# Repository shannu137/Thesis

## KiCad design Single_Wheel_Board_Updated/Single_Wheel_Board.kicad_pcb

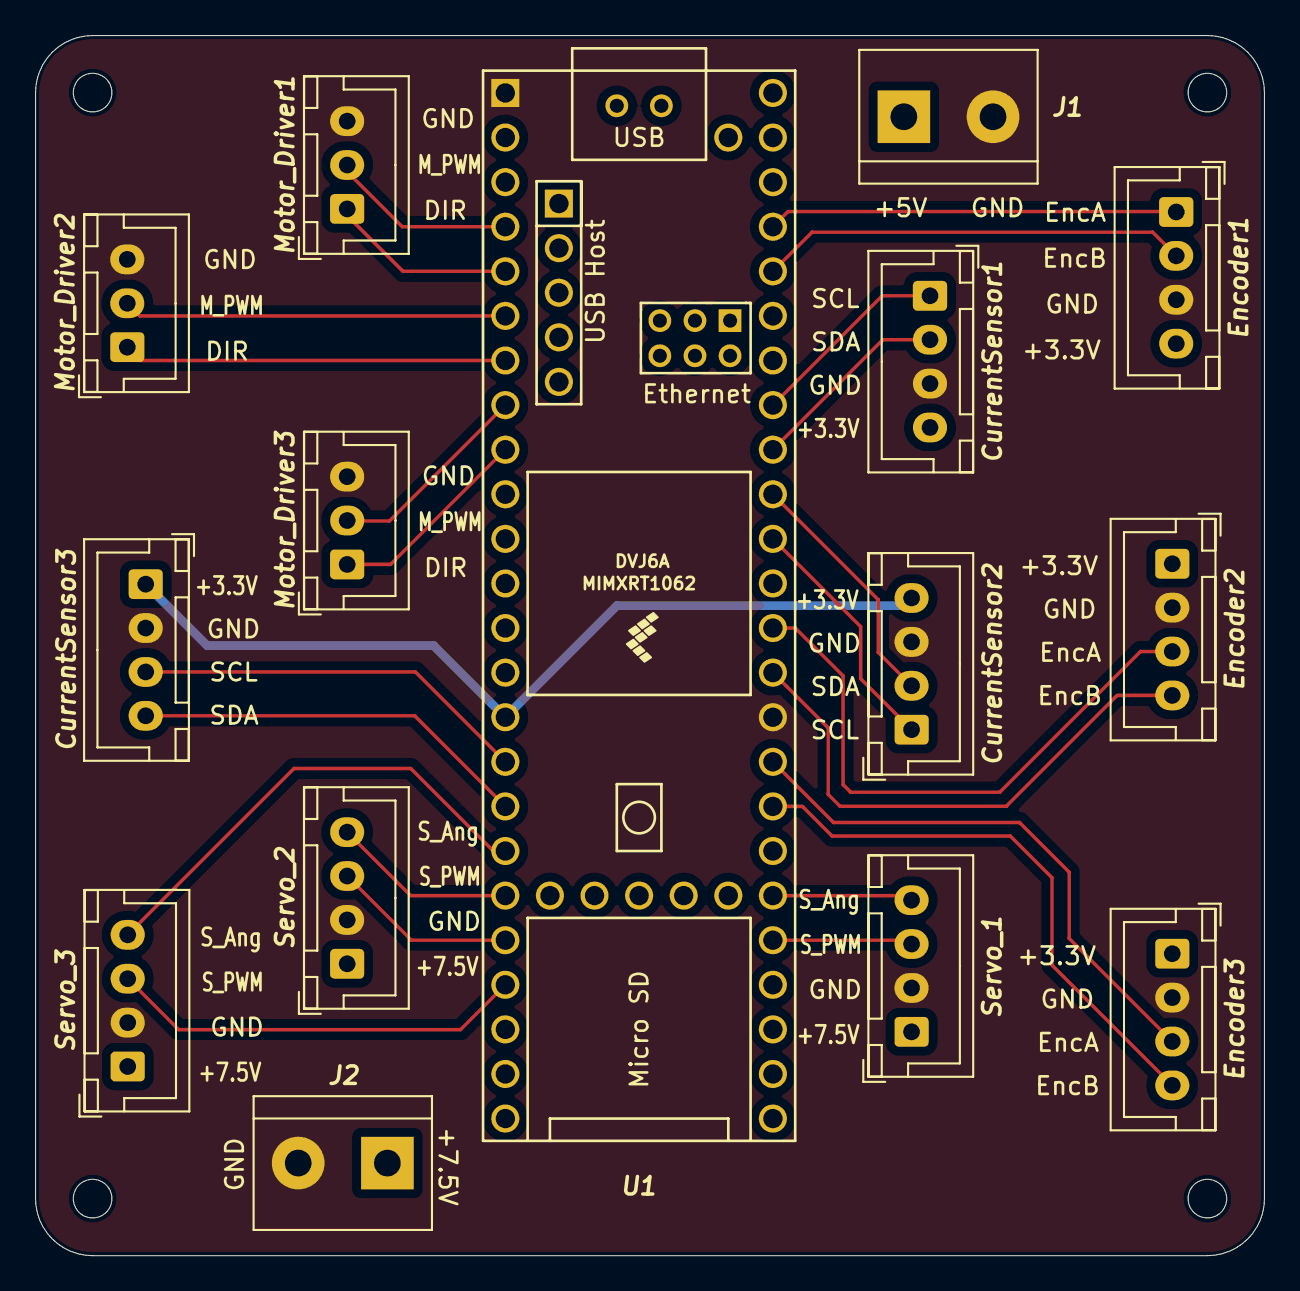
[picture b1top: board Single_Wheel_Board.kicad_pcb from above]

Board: 2 copper layers, 70.0 x 69.5 mm, 15 parts (0 on the bottom side), 28 nets.

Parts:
CurrentSensor1, CurrentSensor2, CurrentSensor3: Conn_01x04; JST_XH_B4B-XH-A_1x04_P2.50mm_Vertical
Encoder1, Encoder2, Encoder3: Conn_01x04; JST_XH_B4B-XH-A_1x04_P2.50mm_Vertical
J1, J2: Screw_Terminal_01x02; TerminalBlock_bornier-2_P5.08mm
Motor_Driver1, Motor_Driver2, Motor_Driver3: Conn_01x03; JST_XH_B3B-XH-A_1x03_P2.50mm_Vertical
Servo_1, Servo_2, Servo_3: Conn_01x04; JST_XH_B4B-XH-A_1x04_P2.50mm_Vertical
U1: Teensy4.1; Teensy41

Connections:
+3.3V: CurrentSensor1.4, CurrentSensor2.4, CurrentSensor3.1, Encoder1.4, Encoder2.1, Encoder3.1, U1.15 (3V3)
+5V: J1.1, U1.48 (VIN)
+7.5V: J2.1, Servo_1.1, Servo_2.1, Servo_3.1
DIR1: Motor_Driver1.1, U1.5 (3_LRCLK2)
DIR2: Motor_Driver2.1, U1.7 (5_IN2)
DIR3: Motor_Driver3.1, U1.9 (7_RX2_OUT1A)
EncA1: Encoder1.1, U1.45 (23_A9_CRX1_MCLK1)
EncA2: Encoder2.3, U1.36 (14_A0_TX3_SPDIF_OUT)
EncA3: Encoder3.3, U1.33 (41_A17)
EncB1: Encoder1.2, U1.44 (22_A8_CTX1)
EncB2: Encoder2.4, U1.35 (13_SCK_LED)
EncB3: Encoder3.4, U1.32 (40_A16)
GND: CurrentSensor1.3, CurrentSensor2.3, CurrentSensor3.2, Encoder1.3, Encoder2.2, Encoder3.2, J1.2, J2.2, Motor_Driver1.3, Motor_Driver2.3, Motor_Driver3.3, Servo_1.2, Servo_2.2, Servo_3.2, U1.1 (GND), U1.34 (GND)
M_PWM1: Motor_Driver1.2, U1.4 (2_OUT2)
M_PWM2: Motor_Driver2.2, U1.6 (4_BCLK2)
M_PWM3: Motor_Driver3.2, U1.8 (6_OUT1D)
SCL1: CurrentSensor1.1, U1.41 (19_A5_SCL)
SCL2: CurrentSensor2.1, U1.38 (16_A2_RX4_SCL1)
SCL3: CurrentSensor3.3, U1.16 (24_A10_TX6_SCL2)
SDA1: CurrentSensor1.2, U1.40 (18_A4_SDA)
SDA2: CurrentSensor2.2, U1.39 (17_A3_TX4_SDA1)
SDA3: CurrentSensor3.4, U1.17 (25_A11_RX6_SDA2)
S_Ang1: Servo_1.4, U1.30 (38_CS1_IN1)
S_Ang2: Servo_2.4, U1.19 (27_A13_SCK1)
S_Ang3: Servo_3.4, U1.18 (26_A12_MOSI1)
S_PWM1: Servo_1.3, U1.29 (37_CS)
S_PWM2: Servo_2.3, U1.20 (28_RX7)
S_PWM3: Servo_3.3, U1.21 (29_TX7)

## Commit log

2026-01-12 Structured_communication
2026-01-14 Format
2026-01-14 14_Jan_Work
2026-01-19 16/01/26
2026-01-19 19/01/26
2026-02-10 fmeca
2026-02-26 init
